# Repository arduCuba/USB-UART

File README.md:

**Programador USB-UART + RTS-DTR**

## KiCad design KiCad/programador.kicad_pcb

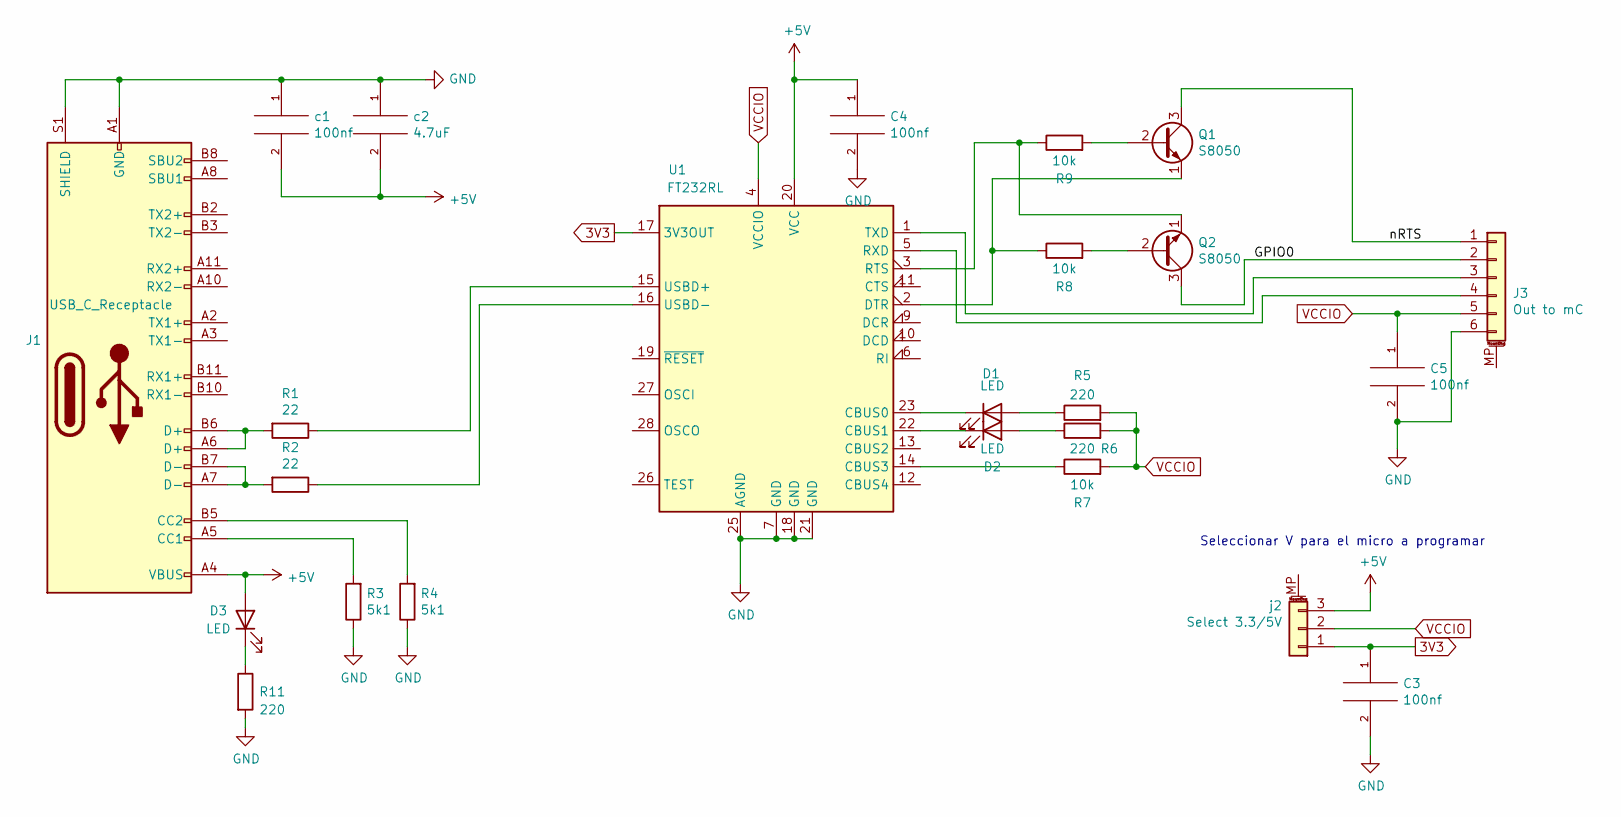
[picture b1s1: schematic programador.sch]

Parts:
C3, C4, C5: 100nf; C_0603_1608Metric_Pad1.08x0.95mm_HandSolder
D1, D2, D3: LED; LED_1206_3216Metric_Pad1.42x1.75mm_HandSolder
J1: USB_C_Receptacle; USB_C_Receptacle_XKB_U262-16XN-4BVC11
J3: Out to mC; PinHeader_1x06_P2.54mm_Vertical
Q1, Q2: S8050; SOT-23
R1, R2: 22; R_0402_1005Metric_Pad0.72x0.64mm_HandSolder
R3, R4: 5k1; R_0402_1005Metric_Pad0.72x0.64mm_HandSolder
R5, R6, R11: 220; R_0402_1005Metric_Pad0.72x0.64mm_HandSolder
R7, R8, R9: 10k; R_0402_1005Metric_Pad0.72x0.64mm_HandSolder
U1: FT232RL; SSOP-28_5.3x10.2mm_P0.65mm
c1: 100nf; C_0603_1608Metric_Pad1.08x0.95mm_HandSolder
c2: 4.7uF; C_0805_2012Metric_Pad1.18x1.45mm_HandSolder
j2: Select 3.3/5V; PinHeader_1x03_P2.54mm_Vertical

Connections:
3V3: C3.1, U1.17 (3V3OUT), j2.1
+5V: C4.1, D3.2 (A), J1.A4 (VBUS), J1.A9 (VBUS), J1.B4 (VBUS), J1.B9 (VBUS), U1.20 (VCC), c1.2, c2.2, j2.3
/GPIO0: J3.2, Q2.3 (C)
/nRTS: J3.1, Q1.3 (C)
/rx_-: J3.4, U1.5 (RXD)
/tx_+: J3.3, U1.1 (TXD)
GND: C3.2, C4.2, C5.2, J1.A1 (GND), J1.A12 (GND), J1.B1 (GND), J1.B12 (GND), J1.S1 (SHIELD), J3.6, R3.1, R4.1, R11.2, U1.7 (GND), U1.18 (GND), U1.21 (GND), U1.25 (AGND), c1.1, c2.1
unnamed: D1.1 (K), U1.23 (CBUS0)
unnamed: D1.2 (A), R5.1
unnamed: D2.1 (K), U1.22 (CBUS1)
unnamed: D2.2 (A), R6.1
unnamed: D3.1 (K), R11.1
unnamed: J1.A5 (CC1), R3.2
unnamed: J1.A6 (D+), J1.B6 (D+), R1.2
unnamed: J1.A7 (D-), J1.B7 (D-), R2.2
unnamed: J1.B5 (CC2), R4.2
unnamed: Q1.1 (E), R8.1, U1.2 (DTR)
unnamed: Q1.2 (B), R9.2
unnamed: Q2.1 (E), R9.1, U1.3 (RTS)
unnamed: Q2.2 (B), R8.2
unnamed: R1.1, U1.15 (USBD+)
unnamed: R2.1, U1.16 (USBD-)
unnamed: R7.1, U1.14 (CBUS3)
VCCIO: C5.1, J3.5, R5.2, R6.2, R7.2, U1.4 (VCCIO), j2.2

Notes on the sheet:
Seleccionar V para el micro a programar

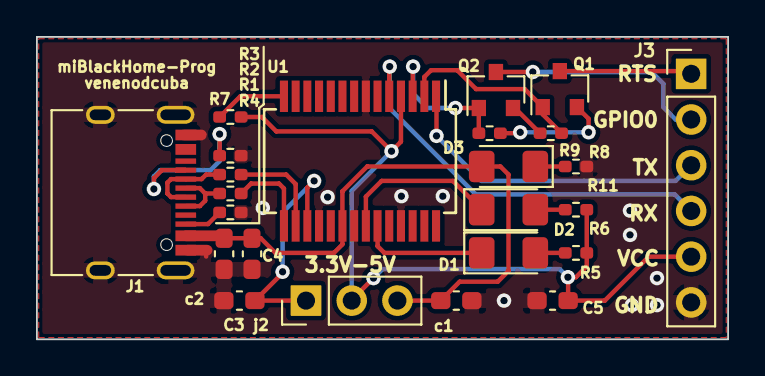
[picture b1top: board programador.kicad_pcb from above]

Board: 2 copper layers, 38.4 x 16.8 mm, 24 parts (0 on the bottom side), 24 nets.
